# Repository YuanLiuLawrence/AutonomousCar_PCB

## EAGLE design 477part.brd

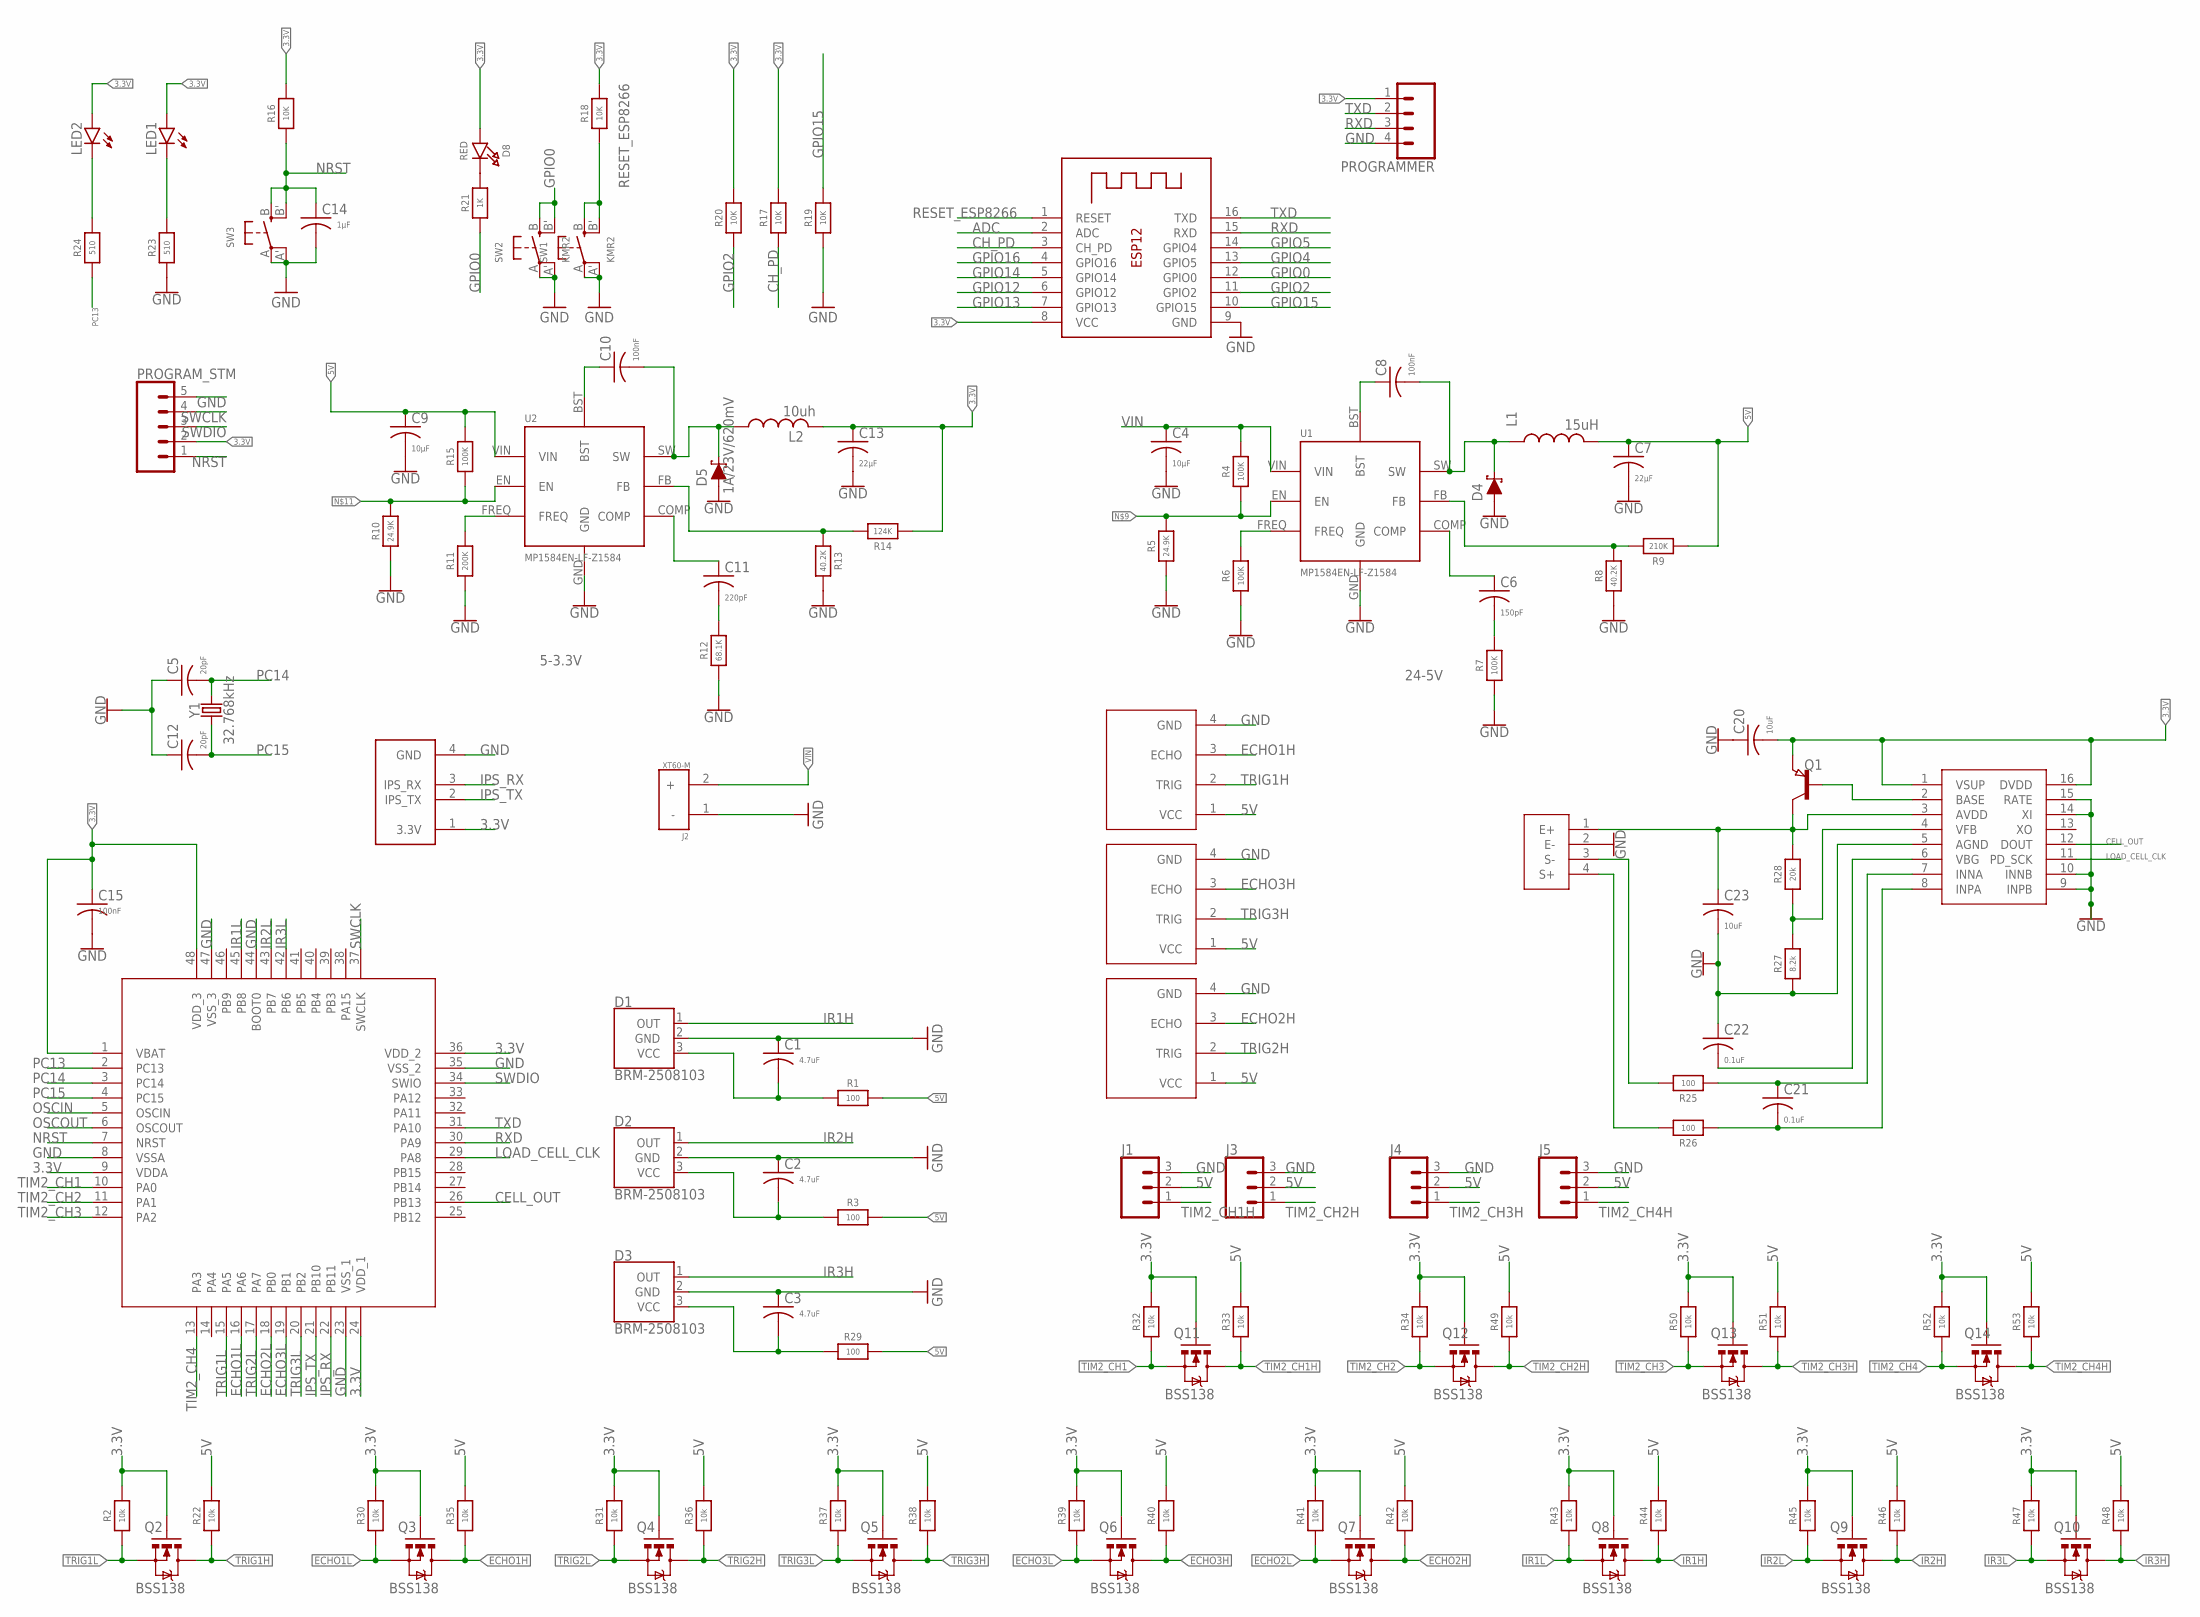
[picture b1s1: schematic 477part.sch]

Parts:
C1, C2, C3: 4.7uF; C0603
C4, C9: 10μF; C0603
C5, C12: 20pF; C0603
C6: 150pF; C0603
C7, C13: 22μF; C0603
C8, C10, C15: 100nF; C0603
C11: 220pF; C0603
C14: 1µF; C0603
C20, C23: 10uF; C0603
C21, C22: 0.1uF; C0603
D1, D2, D3: BRM-2508103; 1X03
D4, D5: 1A/23V/620mV; SOD-323
D8: RED; CHIPLED_0805_NOOUTLINE
ESP8266: ESP-8266; ESP-12
HC_SR04_1, HC_SR04_2, HC_SR04_3: ULTRA_4; 1X04
J1, J3, J4, J5: CONN_03; 1X03
J2: XT60-M; AMASS_XT60-M
L1: 15uH; INDUCTOR2
L2: 10uh; INDUCTOR
LED1, LED2: LEDCHIP-LED0603; CHIP-LED0603
PROGRAMMER: CONN_04; 1X04
PROGRAM_STM: CONN_05; 1X05
Q1: PNP-TRANSISTOR_SOT23; SOT23
Q2, Q3, Q4, Q5, Q6, Q7, Q8, Q9, Q10, Q11, Q12, Q13, Q14: BSS138; SOT23-3
R1, R3, R25, R26, R29: 100; 0805-NO
R2, R22, R30, R31, R32, R33, R34, R35, R36, R37, R38, R39, R40, R41, R42, R43, R44, R45, R46, R47, R48, R49, R50, R51, R52, R53: 10k; 0805-NO
R4, R6, R7, R15: 100K; 0805-NO
R5, R10: 24.9K; 0805-NO
R8, R13: 40.2K; 0805-NO
R9: 210K; 0805-NO
R11: 200K; 0805-NO
R12: 68.1K; 0805-NO
R14: 124K; 0805-NO
R16, R17, R18, R19, R20: 10K; 0805-NO
R21: 1K; 0805-NO
R23, R24: 510; 0805-NO
R27: 8.2k; 0805-NO
R28: 20k; 0805-NO
STM32F1: STM32F1LQFP48; LQFP-48
SW1, SW2, SW3: KMR2; BTN_KMR2_4.6X2.8
U1, U2: MP1584EN-LF-Z1584; MP1584_V2
U$1: IPS_G4; 1X04
U$9: FSR_SR; 1X04
U$10: HX711; SO16A
Y1: 32.768kHz; CRYSTAL-SMD-3.2X1.5MM

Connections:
3.3V: C13.1, C15.1, C20.2, D8.A, ESP8266.8 (VCC), L2.P$2 (2), LED1.A, LED2.A, PROGRAMMER.1, PROGRAM_STM.2, Q1.2 (E), Q2.1 (G), Q3.1 (G), Q4.1 (G), Q5.1 (G), Q6.1 (G), Q7.1 (G), Q8.1 (G), Q9.1 (G), Q10.1 (G), Q11.1 (G), Q12.1 (G), Q13.1 (G), Q14.1 (G), R2.2, R14.1, R16.2, R17.2, R18.2, R20.2, R30.2, R31.2, R32.2, R34.2, R37.2, R39.2, R41.2, R43.2, R45.2, R47.2, R50.2, R52.2, STM32F1.1 (VBAT), STM32F1.9 (VDDA), STM32F1.24 (VDD_1), STM32F1.36 (VDD_2), STM32F1.48 (VDD_3), U$1.1 (3.3V), U$10.1 (VSUP), U$10.16 (DVDD)
5V: C7.1, C9.1, HC_SR04_1.1 (VCC), HC_SR04_2.1 (VCC), HC_SR04_3.1 (VCC), J1.2, J3.2, J4.2, J5.2, L1.P$2 (2), R1.2, R3.2, R9.1, R15.2, R22.2, R29.2, R33.2, R35.2, R36.2, R38.2, R40.2, R42.2, R44.2, R46.2, R48.2, R49.2, R51.2, R53.2, U2.VIN
ADC: ESP8266.2 (ADC)
BASE: Q1.1 (B), U$10.2 (BASE)
BST: C8.1, U1.BST
BST@2: C10.1, U2.BST
CELL_OUT: STM32F1.26 (PB13), U$10.12 (DOUT)
CH_PD: ESP8266.3 (CH_PD), R17.1
COMP: C6.1, U1.COMP
COMP@2: C11.1, U2.COMP
ECHO1H: HC_SR04_1.3 (ECHO), Q3.3 (D), R35.1
ECHO1L: Q3.2 (S), R30.1, STM32F1.16 (PA6)
ECHO2H: HC_SR04_3.3 (ECHO), Q7.3 (D), R42.1
ECHO2L: Q7.2 (S), R41.1, STM32F1.18 (PB0)
ECHO3H: HC_SR04_2.3 (ECHO), Q6.3 (D), R40.1
ECHO3L: Q6.2 (S), R39.1, STM32F1.19 (PB1)
FB: R8.2, R9.2, U1.FB
FB@2: R13.1, R14.2, U2.FB
FREQ: R6.2, U1.FREQ
FREQ@2: R11.2, U2.FREQ
GND: C1.1, C2.1, C3.1, C4.2, C5.1, C7.2, C9.2, C12.1, C13.2, C14.2, C15.2, C20.1, C22.1, C23.2, D1.2 (GND), D2.2 (GND), D3.2 (GND), D4.A, D5.A, ESP8266.9 (GND), HC_SR04_1.4 (GND), HC_SR04_2.4 (GND), HC_SR04_3.4 (GND), J1.3, J2.1 (-), J3.3, J4.3, J5.3, PROGRAMMER.4, PROGRAM_STM.5, R5.1, R6.1, R7.1, R8.1, R10.1, R11.1, R12.1, R13.2, R19.1, R23.1, R27.1, STM32F1.8 (VSSA), STM32F1.23 (VSS_1), STM32F1.35 (VSS_2), STM32F1.44 (BOOT0), STM32F1.47 (VSS_3), SW1.A, SW1.A' (P1), SW2.A, SW2.A' (P1), SW3.A, SW3.A' (P1), U1.GND, U2.GND, U$1.4 (GND), U$9.2 (E-), U$10.5 (AGND), U$10.9 (INPB), U$10.10 (INNB), U$10.14 (XI), U$10.15 (RATE)
GPIO0: ESP8266.12 (GPIO0), R21.1, SW2.B (S), SW2.B' (S1)
GPIO2: ESP8266.11 (GPIO2), R20.1
GPIO4: ESP8266.13 (GPIO5)
GPIO5: ESP8266.14 (GPIO4)
GPIO12: ESP8266.6 (GPIO12)
GPIO13: ESP8266.7 (GPIO13)
GPIO14: ESP8266.5 (GPIO14)
GPIO15: ESP8266.10 (GPIO15), R19.2
GPIO16: ESP8266.4 (GPIO16)
INNA: C21.1, R25.1, U$10.7 (INNA)
INPA: C21.2, R26.1, U$10.8 (INPA)
IPS_RX: STM32F1.22 (PB11), U$1.3 (IPS_RX)
IPS_TX: STM32F1.21 (PB10), U$1.2 (IPS_TX)
IR1H: D1.1 (OUT), Q8.3 (D), R44.1
IR1L: Q8.2 (S), R43.1, STM32F1.45 (PB8)
IR2H: D2.1 (OUT), Q9.3 (D), R46.1
IR2L: Q9.2 (S), R45.1, STM32F1.43 (PB7)
IR3H: D3.1 (OUT), Q10.3 (D), R48.1
IR3L: Q10.2 (S), R47.1, STM32F1.42 (PB6)
LOAD_CELL_CLK: STM32F1.29 (PA8), U$10.11 (PD_SCK)
unnamed: C1.2, D1.3 (VCC), R1.1
unnamed: C2.2, D2.3 (VCC), R3.1
unnamed: C11.2, R12.2
unnamed: LED2.C, R24.2
unnamed: C3.2, D3.3 (VCC), R29.1
unnamed: D8.C, R21.2
unnamed: R27.2, R28.1, U$10.4 (VFB)
unnamed: LED1.C, R23.2
unnamed: R4.1, R5.2, U1.EN
unnamed: C6.2, R7.2
unnamed: R10.2, R15.1, U2.EN
unnamed: C22.2, U$10.6 (VBG)
NRST: C14.1, PROGRAM_STM.1, R16.1, STM32F1.7 (NRST), SW3.B (S), SW3.B' (S1)
OSCIN: STM32F1.5 (OSCIN)
OSCOUT: STM32F1.6 (OSCOUT)
PC13: R24.1, STM32F1.2 (PC13)
PC14: C5.2, STM32F1.3 (PC14), Y1.P$2 (2)
PC15: C12.2, STM32F1.4 (PC15), Y1.P$1 (1)
RESET_ESP8266: ESP8266.1 (RESET), R18.1, SW1.B (S), SW1.B' (S1)
RXD: ESP8266.15 (RXD), PROGRAMMER.3, STM32F1.30 (PA9)
S+: R26.2, U$9.4 (S+)
S-: R25.2, U$9.3 (S-)
SW: C8.2, D4.C, L1.P$1 (1), U1.SW
SW@2: C10.2, D5.C, L2.P$1 (1), U2.SW
SWCLK: PROGRAM_STM.4, STM32F1.37 (SWCLK)
SWDIO: PROGRAM_STM.3, STM32F1.34 (SWIO)
TIM2_CH1: Q11.2 (S), R32.1, STM32F1.10 (PA0)
TIM2_CH1H: J1.1, Q11.3 (D), R33.1
TIM2_CH2: Q12.2 (S), R34.1, STM32F1.11 (PA1)
TIM2_CH2H: J3.1, Q12.3 (D), R49.1
TIM2_CH3: Q13.2 (S), R50.1, STM32F1.12 (PA2)
TIM2_CH3H: J4.1, Q13.3 (D), R51.1
TIM2_CH4: Q14.2 (S), R52.1, STM32F1.13 (PA3)
TIM2_CH4H: J5.1, Q14.3 (D), R53.1
TRIG1H: HC_SR04_1.2 (TRIG), Q2.3 (D), R22.1
TRIG1L: Q2.2 (S), R2.1, STM32F1.15 (PA5)
TRIG2H: HC_SR04_3.2 (TRIG), Q4.3 (D), R36.1
TRIG2L: Q4.2 (S), R31.1, STM32F1.17 (PA7)
TRIG3H: HC_SR04_2.2 (TRIG), Q5.3 (D), R38.1
TRIG3L: Q5.2 (S), R37.1, STM32F1.20 (PB2)
TXD: ESP8266.16 (TXD), PROGRAMMER.2, STM32F1.31 (PA10)
VFB: C23.1, Q1.3 (C), R28.2, U$9.1 (E+), U$10.3 (AVDD)
VIN: C4.1, J2.2 (+), R4.2, U1.VIN

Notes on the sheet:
24-5V
5-3.3V

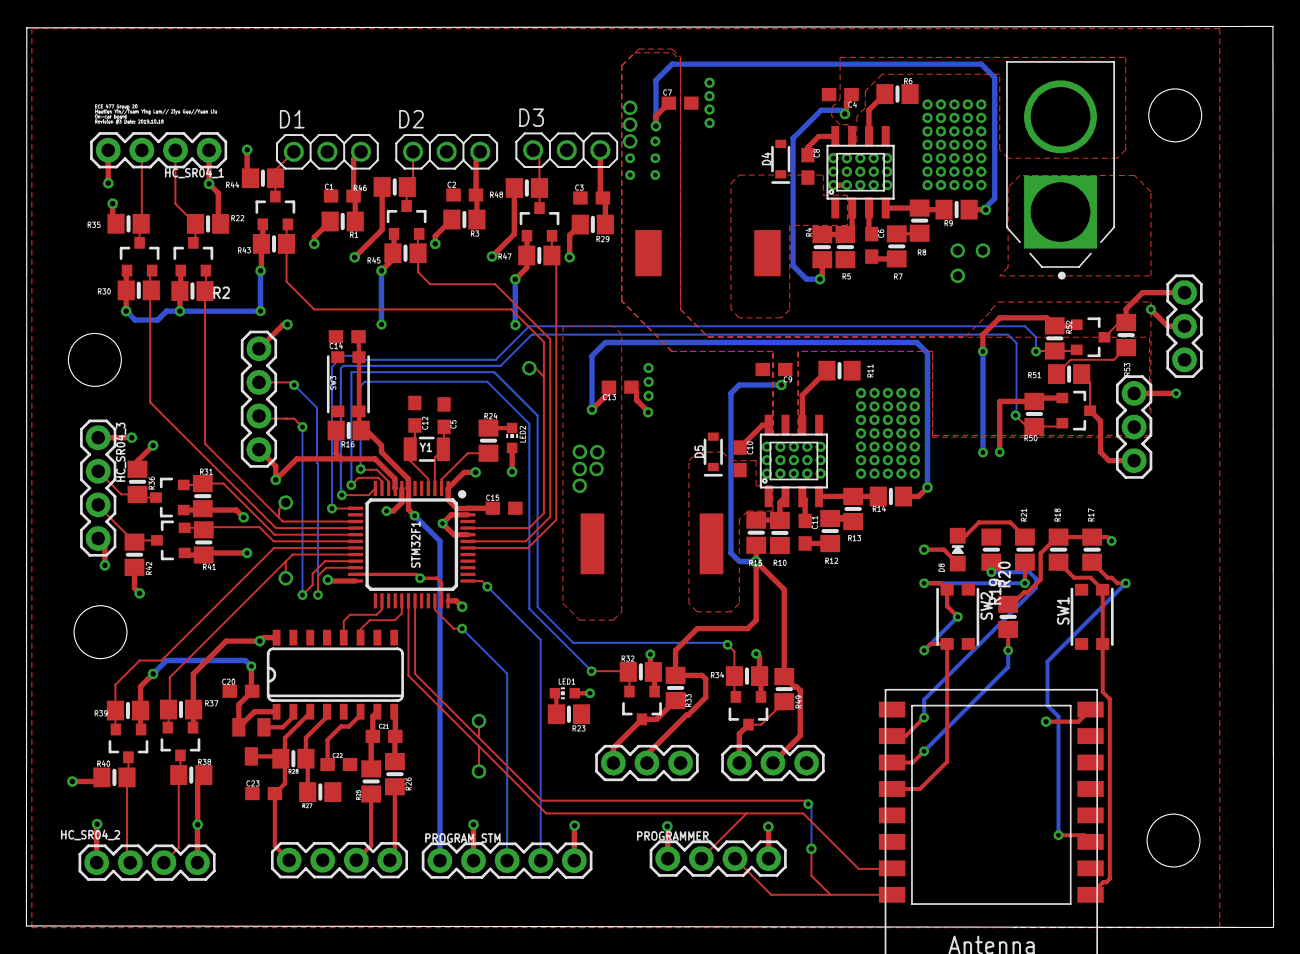
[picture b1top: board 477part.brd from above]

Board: 2 copper layers, 94.3 x 68.1 mm, 117 parts (0 on the bottom side), 75 nets.

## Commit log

2020-05-22 finished commit

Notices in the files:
parts and their libraries:
microbuilder: This work is placed in the public domain, and may be freely used for commercial and non-commercial work with the following conditions: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
SparkFun-Connectors: Licensing: Creative Commons ShareAlike 4.0 International - https://creativecommons.org/licenses/by-sa/4.0
